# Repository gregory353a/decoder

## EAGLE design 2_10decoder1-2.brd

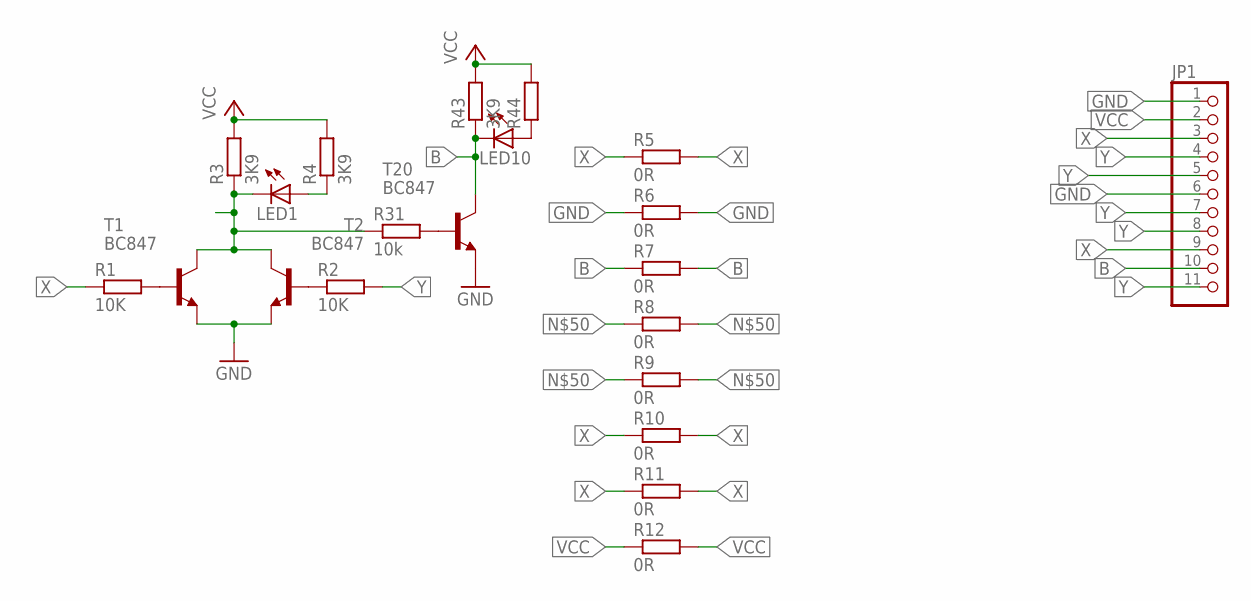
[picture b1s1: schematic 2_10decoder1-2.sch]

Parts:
JP1: PINHD-1X11_2.54-SMD-90°; 1X11SMD/90
LED1, LED10: LEDCHIP-LED0805; CHIP-LED0805
R1, R2: 10K; M0805
R3, R4, R43: 3K9; M0805
R5, R6, R7, R8, R9, R10, R11, R12: 0R; M1206
R31: 10k; M0805
R44: R-EU_M0805; M0805
T1, T2, T20: BC847; SOT23

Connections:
B: JP1.10, LED10.C, R7.1, R7.2, R43.1, T20.3 (C)
GND: JP1.1, JP1.6, R6.1, R6.2, T1.2 (E), T2.2 (E), T20.2 (E)
unnamed: R1.2, T1.1 (B)
unnamed: R2.1, T2.1 (B)
unnamed: LED1.A, R4.1
unnamed: R31.2, T20.1 (B)
unnamed: LED10.A, R44.1
unnamed: LED1.C, R3.1, R8.1, R8.2, R9.1, R9.2, R31.1, T1.3 (C), T2.3 (C)
VCC: JP1.2, R3.2, R4.2, R12.1, R12.2, R43.2, R44.2
X: JP1.3, JP1.9, R1.1, R5.1, R5.2, R10.1, R10.2, R11.1, R11.2
Y: JP1.4, JP1.5, JP1.7, JP1.8, JP1.11, R2.2

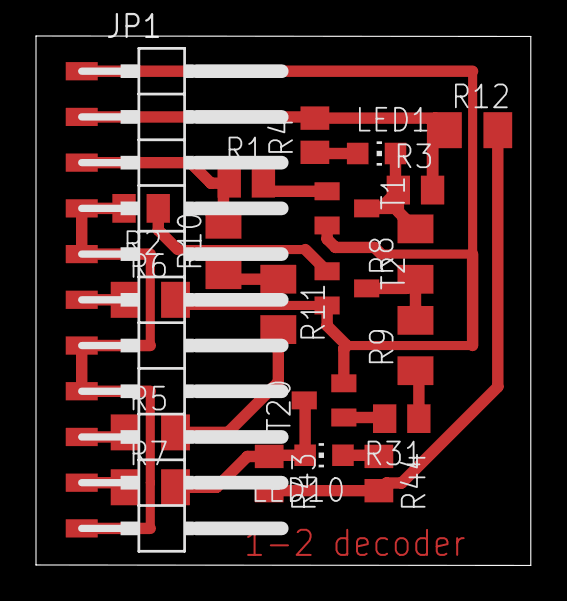
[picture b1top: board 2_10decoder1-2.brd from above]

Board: 2 copper layers, 27.5 x 29.4 mm, 21 parts (0 on the bottom side), 11 nets.

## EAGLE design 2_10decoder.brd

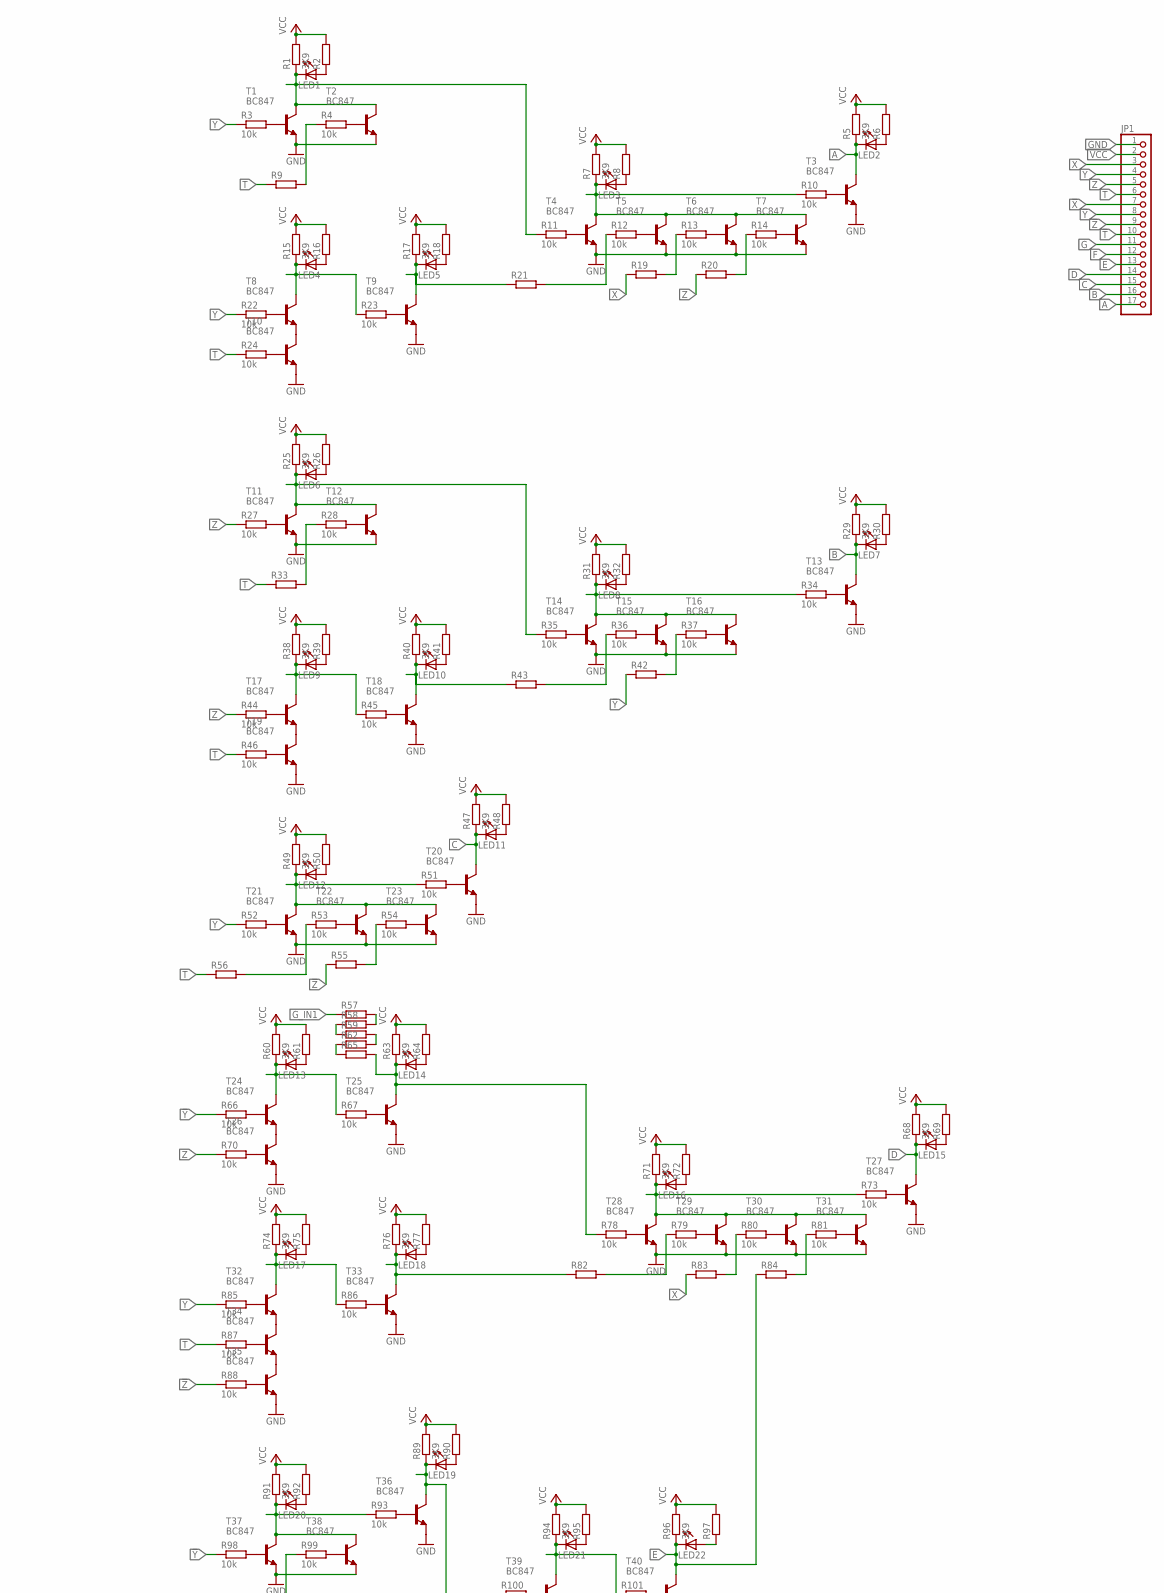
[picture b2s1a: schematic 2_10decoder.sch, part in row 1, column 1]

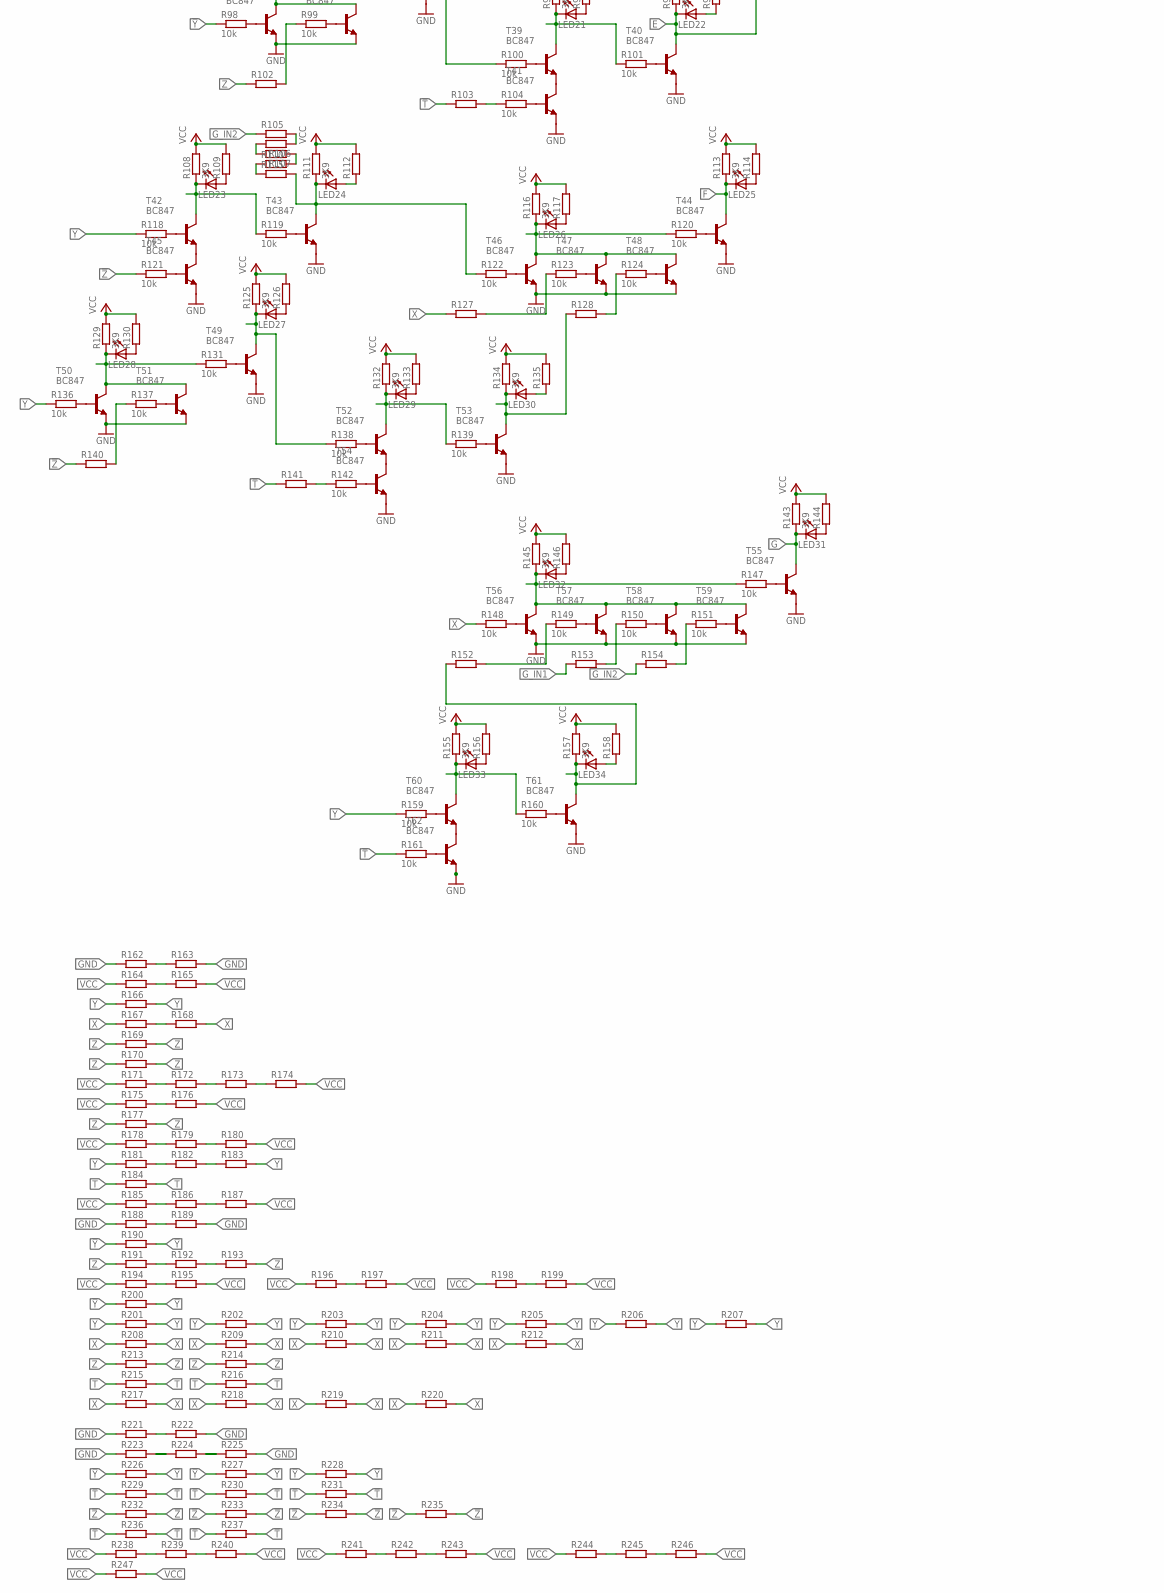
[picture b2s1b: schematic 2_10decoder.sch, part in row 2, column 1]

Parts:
JP1: PINHD-1X17_2.54-SMD-90°; 1X17SMD/90
LED1, LED2, LED3, LED4, LED5, LED6, LED7, LED8, LED9, LED10, LED11, LED12, LED13, LED14, LED15, LED16, LED17, LED18, LED19, LED20, LED21, LED22, LED23, LED24, LED25, LED26, LED27, LED28, LED29, LED30, LED31, LED32, LED33, LED34: LEDCHIP-LED0805; CHIP-LED0805
R1, R5, R7, R15, R17, R25, R29, R31, R38, R40, R47, R49, R60, R63, R68, R71, R74, R76, R89, R91, R94, R96, R108, R111, R113, R116, R125, R129, R132, R134, R143, R145, R155, R157: 3K9; M0805
R2, R6, R8, R16, R18, R26, R30, R32, R39, R41, R48, R50, R61, R64, R69, R72, R75, R77, R90, R92, R95, R97, R109, R112, R114, R117, R126, R130, R133, R135, R144, R146, R156, R158: R-EU_M0805; M0805
R3, R4, R10, R11, R12, R13, R14, R22, R23, R24, R27, R28, R34, R35, R36, R37, R44, R45, R46, R51, R52, R53, R54, R66, R67, R70, R73, R78, R79, R80, R81, R85, R86, R87, R88, R93, R98, R99, R100, R101, R104, R118, R119, R120, R121, R122, R123, R124, R131, R136, R137, R138, R139, R142, R147, R148, R149, R150, R151, R159, R160, R161: 10k; M0805
R9, R19, R20, R21, R33, R42, R43, R55, R56, R57, R58, R59, R62, R65, R82, R83, R84, R102, R103, R105, R106, R107, R110, R115, R127, R128, R140, R141, R152, R153, R154, R162, R163, R164, R165, R166, R167, R168, R169, R170, R171, R172, R173, R174, R175, R176, R177, R178, R179, R180, R181, R182, R183, R184, R185, R186, R187, R188, R189, R190, R191, R192, R193, R194, R195, R196, R197, R198, R199, R200, R201, R202, R203, R204, R205, R206, R207, R208, R209, R210, R211, R212, R213, R214, R215, R216, R217, R218, R219, R220, R221, R222, R223, R224, R225, R226, R227, R228, R229, R230, R231, R232, R233, R234, R235, R236, R237, R238, R239, R240, R241, R242, R243, R244, R245, R246, R247: R-EU_M1206; M1206
T1, T2, T3, T4, T5, T6, T7, T8, T9, T10, T11, T12, T13, T14, T15, T16, T17, T18, T19, T20, T21, T22, T23, T24, T25, T26, T27, T28, T29, T30, T31, T32, T33, T34, T35, T36, T37, T38, T39, T40, T41, T42, T43, T44, T45, T46, T47, T48, T49, T50, T51, T52, T53, T54, T55, T56, T57, T58, T59, T60, T61, T62: BC847; SOT23

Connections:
!T: JP1.10, R103.1, R141.1, R161.1, R229.1, R229.2, R230.1, R230.2, R231.1, R231.2, R236.1, R236.2, R237.1, R237.2
!X: JP1.7
!Y: JP1.8, R42.1, R66.1, R98.1, R190.1, R190.2, R200.1, R200.2, R226.1, R226.2, R227.1, R227.2, R228.1, R228.2
!Z: JP1.9, R55.1, R88.1, R121.1, R140.1, R232.1, R232.2, R233.1, R233.2, R234.1, R234.2, R235.1, R235.2
A: JP1.17, LED2.C, R5.1, T3.3 (C)
B: JP1.16, LED7.C, R29.1, T13.3 (C)
C: JP1.15, LED11.C, R47.1, T20.3 (C)
D: JP1.14, LED15.C, R68.1, T27.3 (C)
E: JP1.13, LED22.C, R84.1, R96.1, T40.3 (C)
F: JP1.12, LED25.C, R113.1, T44.3 (C)
G: JP1.11, LED31.C, R143.1, T55.3 (C)
GND: JP1.1, R162.1, R163.2, R188.1, R188.2, R189.1, R189.2, R221.1, R221.2, R222.1, R222.2, R223.1, R223.2, R224.1, R224.2, R225.1, R225.2, T1.2 (E), T2.2 (E), T3.2 (E), T4.2 (E), T5.2 (E), T6.2 (E), T7.2 (E), T9.2 (E), T10.2 (E), T11.2 (E), T12.2 (E), T13.2 (E), T14.2 (E), T15.2 (E), T16.2 (E), T18.2 (E), T19.2 (E), T20.2 (E), T21.2 (E), T22.2 (E), T23.2 (E), T25.2 (E), T26.2 (E), T27.2 (E), T28.2 (E), T29.2 (E), T30.2 (E), T31.2 (E), T33.2 (E), T35.2 (E), T36.2 (E), T37.2 (E), T38.2 (E), T40.2 (E), T41.2 (E), T43.2 (E), T44.2 (E), T45.2 (E), T46.2 (E), T47.2 (E), T48.2 (E), T49.2 (E), T50.2 (E), T51.2 (E), T53.2 (E), T54.2 (E), T55.2 (E), T56.2 (E), T57.2 (E), T58.2 (E), T59.2 (E), T61.2 (E), T62.2 (E)
G_IN1: R57.1, R153.1
G_IN2: R105.1, R154.1
unnamed: LED4.A, R16.1
unnamed: LED4.C, R15.1, R23.1, T8.3 (C)
unnamed: R3.2, T1.1 (B)
unnamed: R4.2, T2.1 (B)
unnamed: R22.2, T8.1 (B)
unnamed: R23.2, T9.1 (B)
unnamed: R24.2, T10.1 (B)
unnamed: R11.2, T4.1 (B)
unnamed: R10.2, T3.1 (B)
unnamed: R12.2, T5.1 (B)
unnamed: R13.2, T6.1 (B)
unnamed: R14.2, T7.1 (B)
unnamed: LED1.A, R2.1
unnamed: LED1.C, R1.1, R11.1, T1.3 (C), T2.3 (C)
unnamed: R4.1, R9.2
unnamed: R103.2, R104.1
unnamed: LED3.A, R8.1
unnamed: LED3.C, R7.1, R10.1, T4.3 (C), T5.3 (C), T6.3 (C), T7.3 (C)
unnamed: LED5.A, R18.1
unnamed: LED5.C, R17.1, R21.1, T9.3 (C)
unnamed: LED2.A, R6.1
unnamed: R141.2, R142.1
unnamed: T8.2 (E), T10.3 (C)
unnamed: R12.1, R21.2
unnamed: R106.2, R107.2
unnamed: R110.1, R115.1
unnamed: R27.2, T11.1 (B)
unnamed: R28.2, T12.1 (B)
unnamed: R13.1, R19.2
unnamed: R14.1, R20.2
unnamed: R44.2, T17.1 (B)
unnamed: R45.2, T18.1 (B)
unnamed: R46.2, T19.1 (B)
unnamed: R35.2, T14.1 (B)
unnamed: R34.2, T13.1 (B)
unnamed: R36.2, T15.1 (B)
unnamed: R37.2, T16.1 (B)
unnamed: R105.2, R106.1
unnamed: LED6.A, R26.1
unnamed: LED6.C, R25.1, R35.1, T11.3 (C), T12.3 (C)
unnamed: R28.1, R33.2
unnamed: R107.1, R110.2
unnamed: LED9.A, R39.1
unnamed: LED9.C, R38.1, R45.1, T17.3 (C)
unnamed: LED8.A, R32.1
unnamed: LED8.C, R31.1, R34.1, T14.3 (C), T15.3 (C), T16.3 (C)
unnamed: LED10.A, R41.1
unnamed: LED10.C, R40.1, R43.1, T18.3 (C)
unnamed: LED7.A, R30.1
unnamed: R62.1, R65.1
unnamed: T17.2 (E), T19.3 (C)
unnamed: R59.2, R62.2
unnamed: R58.1, R59.1
unnamed: R37.1, R42.2
unnamed: R57.2, R58.2
unnamed: R36.1, R43.2
unnamed: R52.2, T21.1 (B)
unnamed: R51.2, T20.1 (B)
unnamed: R53.2, T22.1 (B)
unnamed: R54.2, T23.1 (B)
unnamed: R78.2, T28.1 (B)
unnamed: R73.2, T27.1 (B)
unnamed: LED12.A, R50.1
unnamed: LED12.C, R49.1, R51.1, T21.3 (C), T22.3 (C), T23.3 (C)
unnamed: R79.2, T29.1 (B)
unnamed: LED11.A, R48.1
unnamed: R162.2, R163.1
unnamed: R54.1, R55.2
unnamed: R80.2, T30.1 (B)
unnamed: R53.1, R56.2
unnamed: R81.2, T31.1 (B)
unnamed: R164.2, R165.1
unnamed: LED16.A, R72.1
unnamed: LED16.C, R71.1, R73.1, T28.3 (C), T29.3 (C), T30.3 (C), T31.3 (C)
unnamed: R85.2, T32.1 (B)
unnamed: LED15.A, R69.1
unnamed: R167.2, R168.1
unnamed: R80.1, R83.2
unnamed: R81.1, R84.2
unnamed: R79.1, R82.2
unnamed: T34.2 (E), T35.3 (C)
unnamed: R67.2, T25.1 (B)
unnamed: R70.2, T26.1 (B)
unnamed: LED13.A, R61.1
unnamed: LED13.C, R60.1, R67.1, T24.3 (C)
unnamed: LED14.A, R64.1
unnamed: R86.2, T33.1 (B)
unnamed: T24.2 (E), T26.3 (C)
unnamed: R122.2, T46.1 (B)
unnamed: R171.2, R172.1
unnamed: R87.2, T34.1 (B)
unnamed: LED17.A, R75.1
unnamed: R123.2, T47.1 (B)
unnamed: LED18.A, R77.1
unnamed: T32.2 (E), T34.3 (C)
unnamed: R159.2, T60.1 (B)
unnamed: R173.2, R174.1
unnamed: LED18.C, R76.1, R82.1, T33.3 (C)
unnamed: R88.2, T35.1 (B)
unnamed: LED26.A, R117.1
unnamed: R98.2, T37.1 (B)
unnamed: R99.2, T38.1 (B)
unnamed: LED20.A, R92.1
unnamed: LED20.C, R91.1, R93.1, T37.3 (C), T38.3 (C)
unnamed: LED26.C, R116.1, R120.1, T46.3 (C), T47.3 (C), T48.3 (C)
unnamed: LED25.A, R114.1
unnamed: R93.2, T36.1 (B)
unnamed: R100.2, T39.1 (B)
unnamed: LED19.A, R90.1
unnamed: R175.2, R176.1
unnamed: R101.2, T40.1 (B)
unnamed: R178.2, R179.1
unnamed: R181.2, R182.1
unnamed: R124.1, R128.2
unnamed: R123.1, R127.2
unnamed: R185.2, R186.1
unnamed: R191.2, R192.1
unnamed: R121.2, T45.1 (B)
unnamed: LED17.C, R74.1, R86.1, T32.3 (C)
unnamed: R194.2, R195.1
unnamed: LED23.A, R109.1
unnamed: R196.2, R197.1
unnamed: R198.2, R199.1
unnamed: R238.2, R239.1
unnamed: T42.2 (E), T45.3 (C)
unnamed: R241.2, R242.1
unnamed: R104.2, T41.1 (B)
unnamed: R244.2, R245.1
unnamed: LED21.C, R94.1, R101.1, T39.3 (C)
unnamed: R136.2, T50.1 (B)
unnamed: R99.1, R102.2
unnamed: R131.2, T49.1 (B)
unnamed: R138.2, T52.1 (B)
unnamed: LED19.C, R89.1, R100.1, T36.3 (C)
unnamed: T39.2 (E), T41.3 (C)
unnamed: LED21.A, R95.1
unnamed: R139.2, T53.1 (B)
unnamed: LED29.C, R132.1, R139.1, T52.3 (C)
unnamed: T52.2 (E), T54.3 (C)
unnamed: LED27.C, R125.1, R138.1, T49.3 (C)
unnamed: R147.2, T55.1 (B)
unnamed: R149.2, T57.1 (B)
unnamed: R150.2, T58.1 (B)
unnamed: R151.2, T59.1 (B)
unnamed: R150.1, R153.2
unnamed: R149.1, R152.2
unnamed: R151.1, R154.2
unnamed: R160.2, T61.1 (B)
unnamed: R161.2, T62.1 (B)
unnamed: T60.2 (E), T62.3 (C)
unnamed: R66.2, T24.1 (B)
unnamed: LED28.A, R130.1
unnamed: LED28.C, R129.1, R131.1, T50.3 (C), T51.3 (C)
unnamed: LED27.A, R126.1
unnamed: LED29.A, R133.1
unnamed: LED30.C, R128.1, R134.1, T53.3 (C)
unnamed: LED32.A, R146.1
unnamed: LED32.C, R145.1, R147.1, T56.3 (C), T57.3 (C), T58.3 (C), T59.3 (C)
unnamed: LED31.A, R144.1
unnamed: LED33.A, R156.1
unnamed: LED33.C, R155.1, R160.1, T60.3 (C)
unnamed: LED34.C, R152.1, R157.1, T61.3 (C)
unnamed: R120.2, T44.1 (B)
unnamed: R118.2, T42.1 (B)
unnamed: R124.2, T48.1 (B)
unnamed: LED23.C, R108.1, R119.1, T42.3 (C)
unnamed: R119.2, T43.1 (B)
unnamed: R148.2, T56.1 (B)
unnamed: R137.1, R140.2
unnamed: R137.2, T51.1 (B)
unnamed: R142.2, T54.1 (B)
S$2: LED22.A, R97.1
S$4: LED24.A, R112.1
S$5: LED34.A, R158.1
S$40: LED30.A, R135.1
S$123: LED24.C, R111.1, R115.2, R122.1, T43.3 (C)
S$124: LED14.C, R63.1, R65.2, R78.1, T25.3 (C)
T: JP1.6, R9.1, R24.1, R33.1, R46.1, R56.1, R87.1, R184.1, R184.2, R215.1, R215.2, R216.1, R216.2
VCC: JP1.2, R1.2, R2.2, R5.2, R6.2, R7.2, R8.2, R15.2, R16.2, R17.2, R18.2, R25.2, R26.2, R29.2, R30.2, R31.2, R32.2, R38.2, R39.2, R40.2, R41.2, R47.2, R48.2, R49.2, R50.2, R60.2, R61.2, R63.2, R64.2, R68.2, R69.2, R71.2, R72.2, R74.2, R75.2, R76.2, R77.2, R89.2, R90.2, R91.2, R92.2, R94.2, R95.2, R96.2, R97.2, R108.2, R109.2, R111.2, R112.2, R113.2, R114.2, R116.2, R117.2, R125.2, R126.2, R129.2, R130.2, R132.2, R133.2, R134.2, R135.2, R143.2, R144.2, R145.2, R146.2, R155.2, R156.2, R157.2, R158.2, R164.1, R165.2, R171.1, R172.2, R173.1, R174.2, R175.1, R176.2, R178.1, R179.2, R180.1, R180.2, R182.2, R183.1, R185.1, R186.2, R187.1, R187.2, R194.1, R195.2, R196.1, R197.2, R198.1, R199.2, R238.1, R239.2, R240.1, R240.2, R241.1, R242.2, R243.1, R243.2, R244.1, R245.2, R246.1, R246.2, R247.1, R247.2
X: JP1.3, R19.1, R83.1, R127.1, R148.1, R167.1, R168.2, R208.1, R208.2, R209.1, R209.2, R210.1, R210.2, R211.1, R211.2, R212.1, R212.2, R217.1, R217.2, R218.1, R218.2, R219.1, R219.2, R220.1, R220.2
Y: JP1.4, R3.1, R22.1, R52.1, R85.1, R118.1, R136.1, R159.1, R166.1, R166.2, R181.1, R183.2, R201.1, R201.2, R202.1, R202.2, R203.1, R203.2, R204.1, R204.2, R205.1, R205.2, R206.1, R206.2, R207.1, R207.2
Z: JP1.5, R20.1, R27.1, R44.1, R70.1, R102.1, R169.1, R169.2, R170.1, R170.2, R177.1, R177.2, R191.1, R192.2, R193.1, R193.2, R213.1, R213.2, R214.1, R214.2

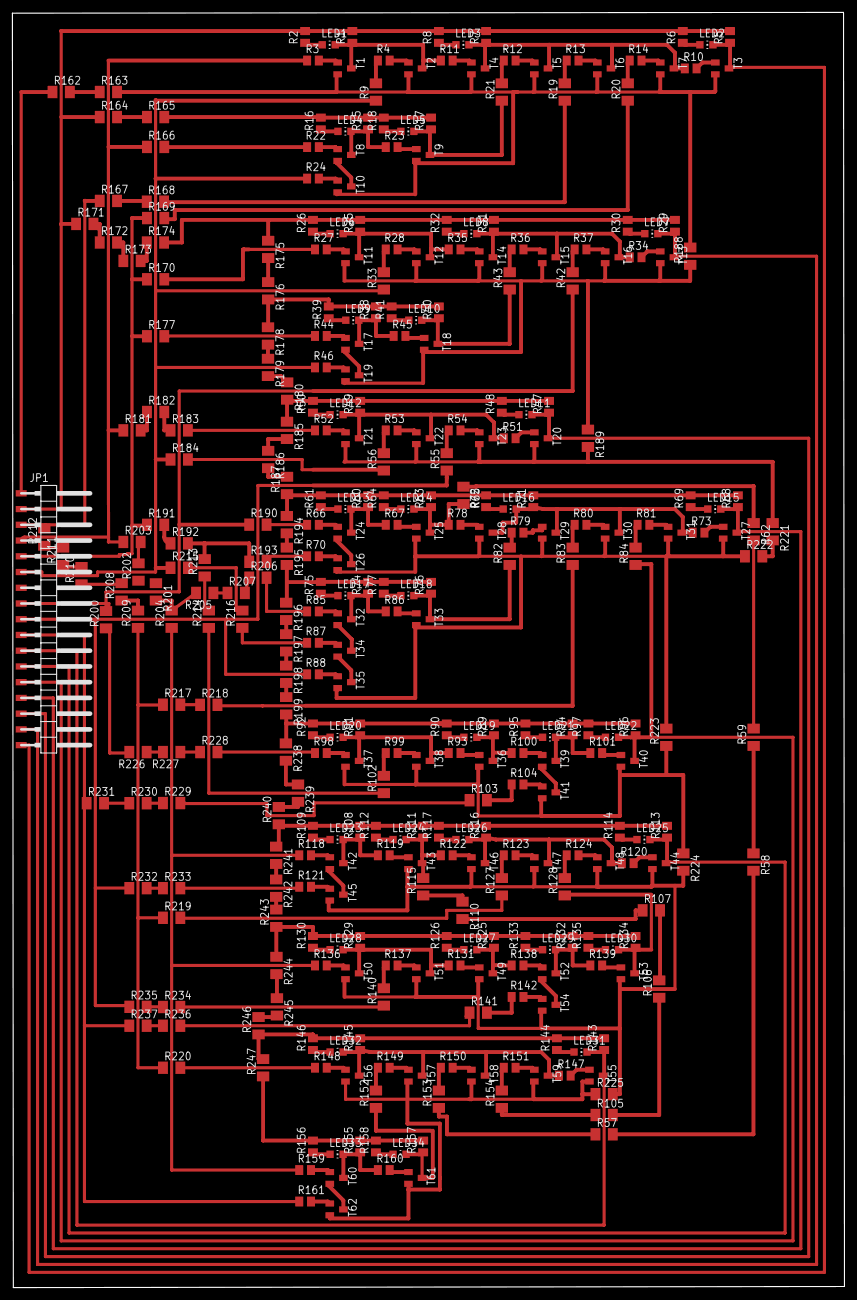
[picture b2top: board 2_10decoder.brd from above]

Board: 2 copper layers, 134.3 x 205.8 mm, 344 parts (0 on the bottom side), 195 nets.

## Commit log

2018-03-16 Init commit fully functional 2_10decoder
2018-03-19 1-2 decoder
2018-03-19 2_10 decoter second approach
2018-03-21 general fix 1-2 decoder
2018-03-21 final schema
2018-03-23 final version of 2_10Decoder
2018-09-12 Fix in 2_10decoder.pdf
2023-07-19 add project file
